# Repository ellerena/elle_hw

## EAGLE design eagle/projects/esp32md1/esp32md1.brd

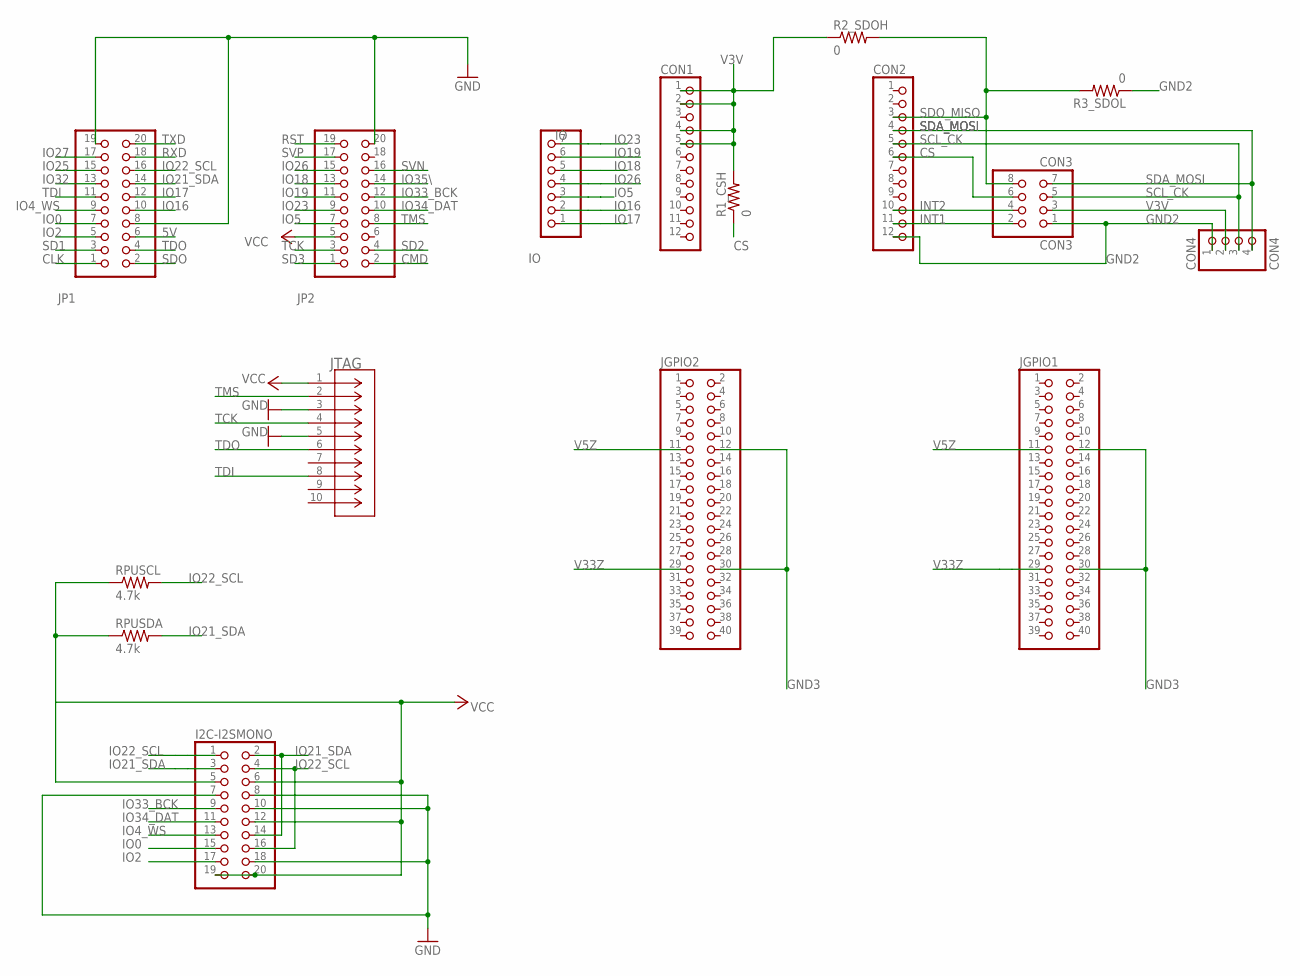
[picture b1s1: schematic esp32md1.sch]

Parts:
CON1, CON2: PINHD-1X12; 1X12
CON3: CON3; 2X04
CON4: CON4; 1X04
I2C-I2SMONO: PINHD-2X10; 2X10
IO: IO; 1X07
JGPIO1, JGPIO2: PINHD-2X20; 2X20
JP1, JP2: PINHD-2X10; 2X10
JTAG: M50-3600542CONN_M50-3600542_HRW-L; CONN_M50-3600542_HRW-L
R1_CSH, R2_SDOH, R3_SDOL: 0; R0402
RPUSCL: 4.7k; R0402
RPUSDA: 4.7k; R0402

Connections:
5V: JP1.6
CLK: JP1.1
CMD: JP2.2
CS: CON2.6, CON3.6, R1_CSH.1
GND: I2C-I2SMONO.7, I2C-I2SMONO.8, I2C-I2SMONO.10, I2C-I2SMONO.18, JP1.8, JP1.19, JP2.20, JTAG.3, JTAG.5
GND2: CON2.12, CON3.1, CON4.1, R3_SDOL.1
GND3: JGPIO1.12, JGPIO1.30, JGPIO2.12, JGPIO2.30
INT1: CON2.11, CON3.2
INT2: CON2.10, CON3.4
IO0: I2C-I2SMONO.15, JP1.7
IO2: I2C-I2SMONO.17, JP1.5
IO4_WS: I2C-I2SMONO.13, JP1.9
IO5: IO.3, JP2.7
IO16: IO.2, JP1.10
IO17: IO.1, JP1.12
IO18: IO.5, JP2.13
IO19: IO.6, JP2.11
IO21_SDA: I2C-I2SMONO.2, I2C-I2SMONO.3, I2C-I2SMONO.14, JP1.14, RPUSDA.2
IO22_SCL: I2C-I2SMONO.1, I2C-I2SMONO.4, I2C-I2SMONO.16, JP1.16, RPUSCL.2
IO23: IO.7, JP2.9
IO25: JP1.15
IO26: IO.4, JP2.15
IO27: JP1.17
IO32: JP1.13
IO33_BCK: I2C-I2SMONO.9, JP2.12
IO34_DAT: I2C-I2SMONO.11, JP2.10
IO35\: JP2.14
RST: JP2.19
RXD: JP1.18
SCL_CK: CON2.5, CON3.5, CON4.3
SD1: JP1.3
SD2: JP2.4
SD3: JP2.1
SDA_MOSI: CON2.4, CON3.7, CON4.4
SDO: JP1.2
SDO_MISO: CON2.3, CON3.8, R2_SDOH.2, R3_SDOL.2
SVN: JP2.16
SVP: JP2.17
TCK: JP2.3, JTAG.4
TDI: JP1.11, JTAG.8
TDO: JP1.4, JTAG.6
TMS: JP2.8, JTAG.2
TXD: JP1.20
V3V: CON1.1, CON1.2, CON1.4, CON1.5, CON3.3, CON4.2, R1_CSH.2, R2_SDOH.1
V5Z: JGPIO1.11, JGPIO2.11
V33Z: JGPIO1.29, JGPIO2.29
VCC: I2C-I2SMONO.5, I2C-I2SMONO.6, I2C-I2SMONO.12, I2C-I2SMONO.19, I2C-I2SMONO.20, JP2.5, JTAG.1, RPUSCL.1, RPUSDA.1

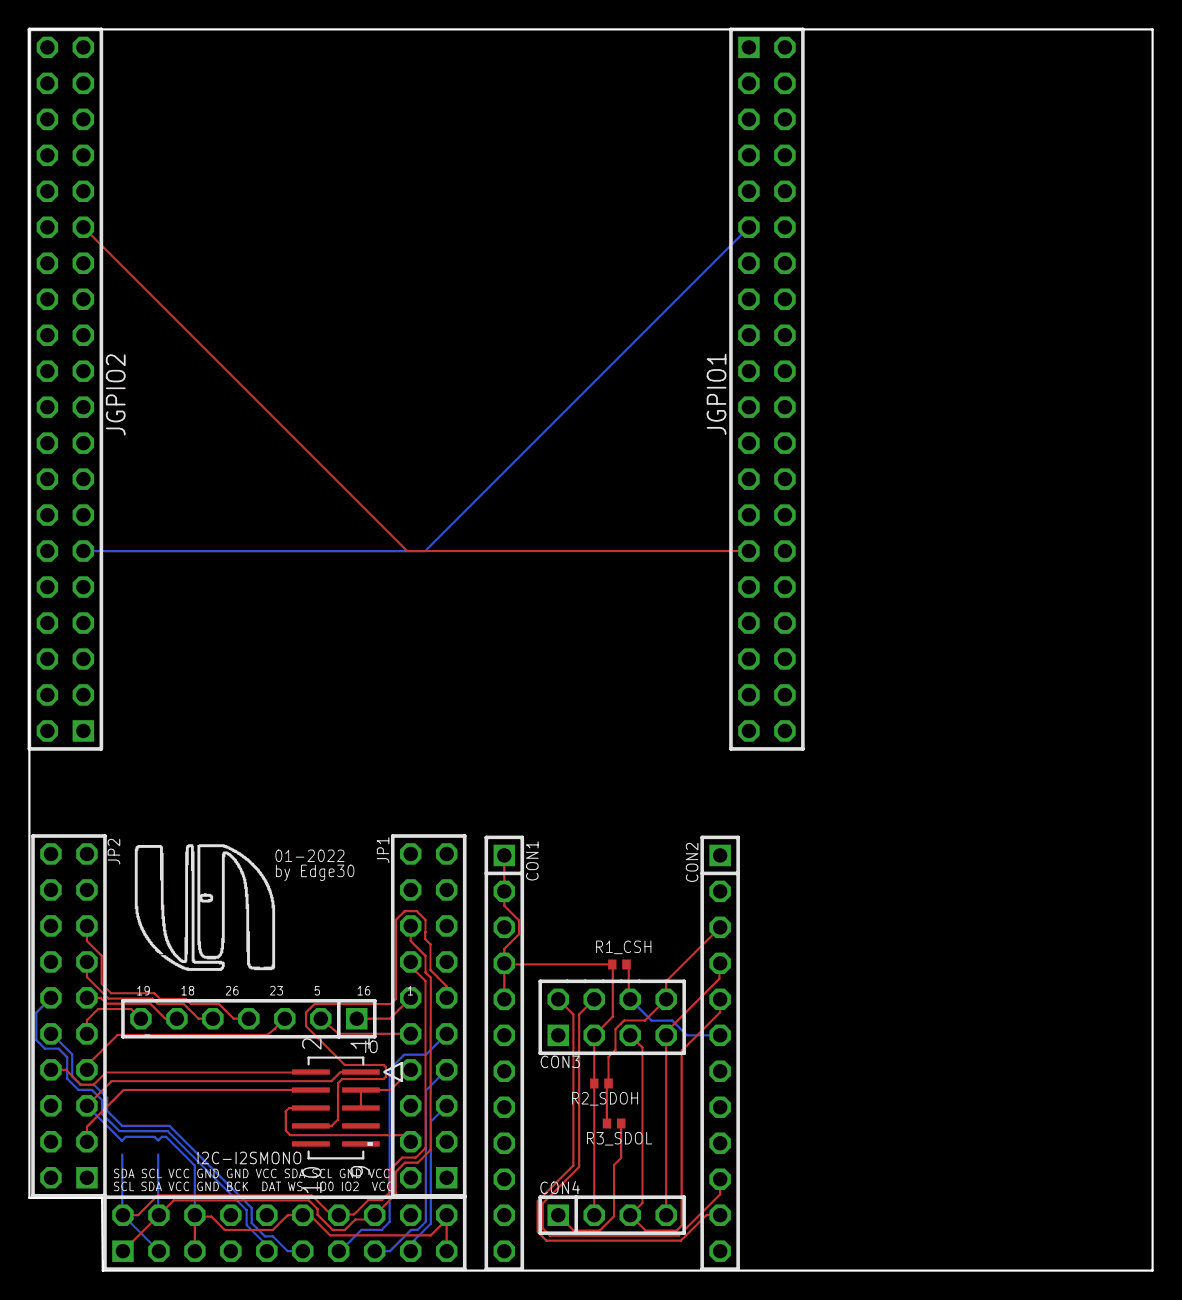
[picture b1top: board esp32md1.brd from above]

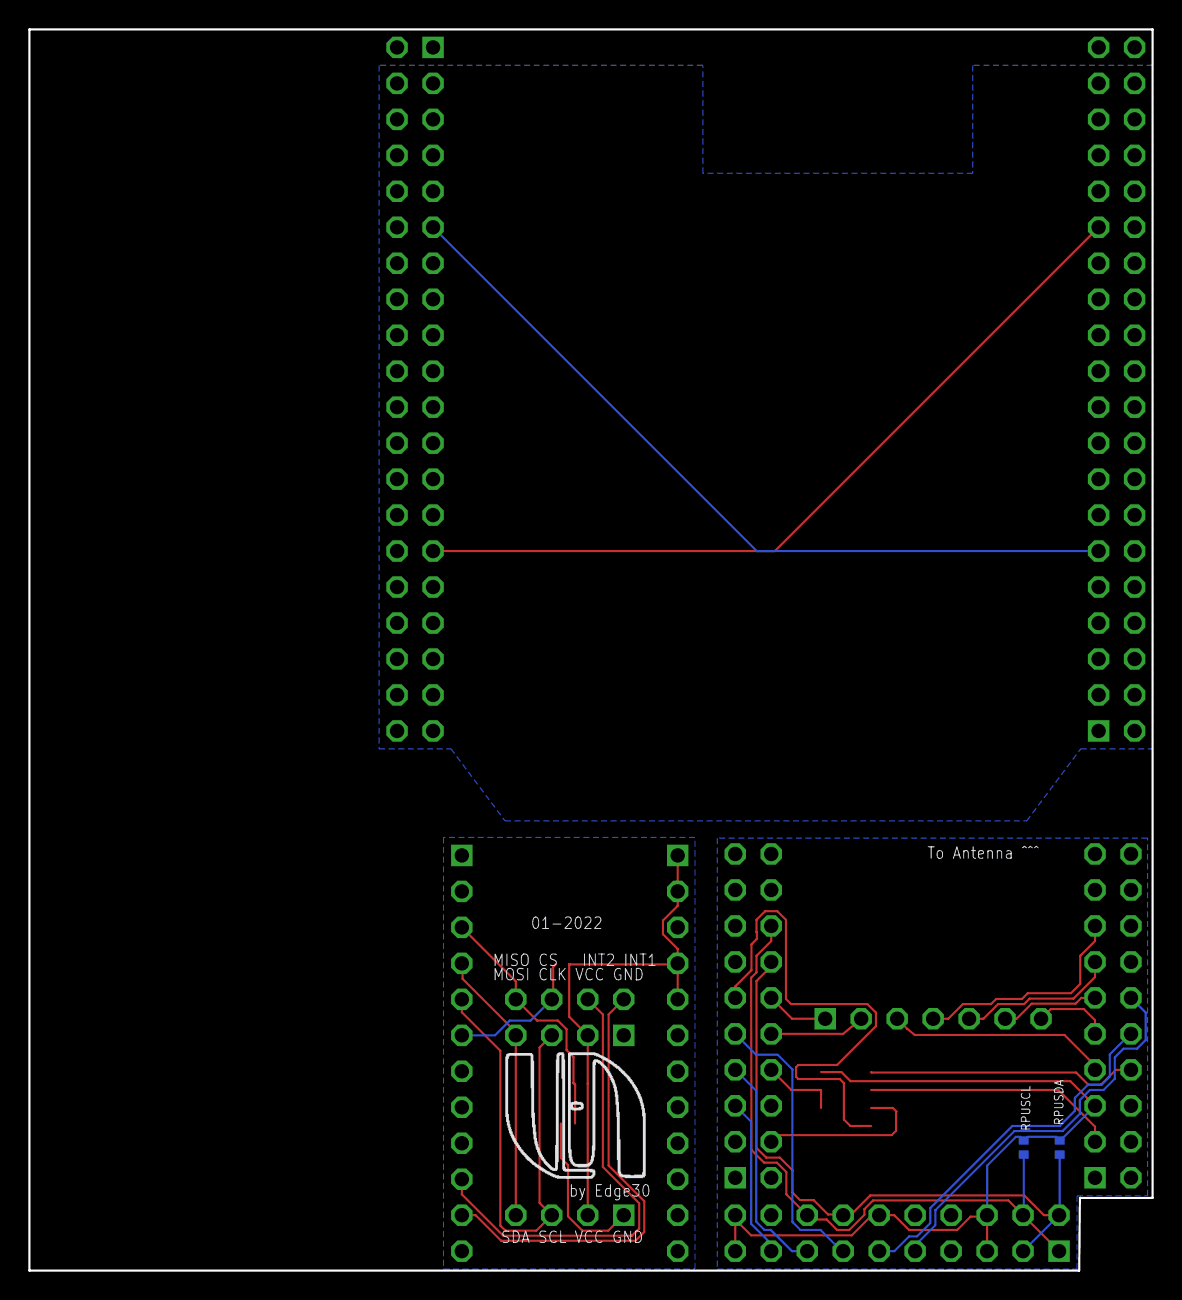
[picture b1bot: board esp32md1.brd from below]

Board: 2 copper layers, 79.3 x 87.6 mm, 16 parts (2 on the bottom side), 31 nets.

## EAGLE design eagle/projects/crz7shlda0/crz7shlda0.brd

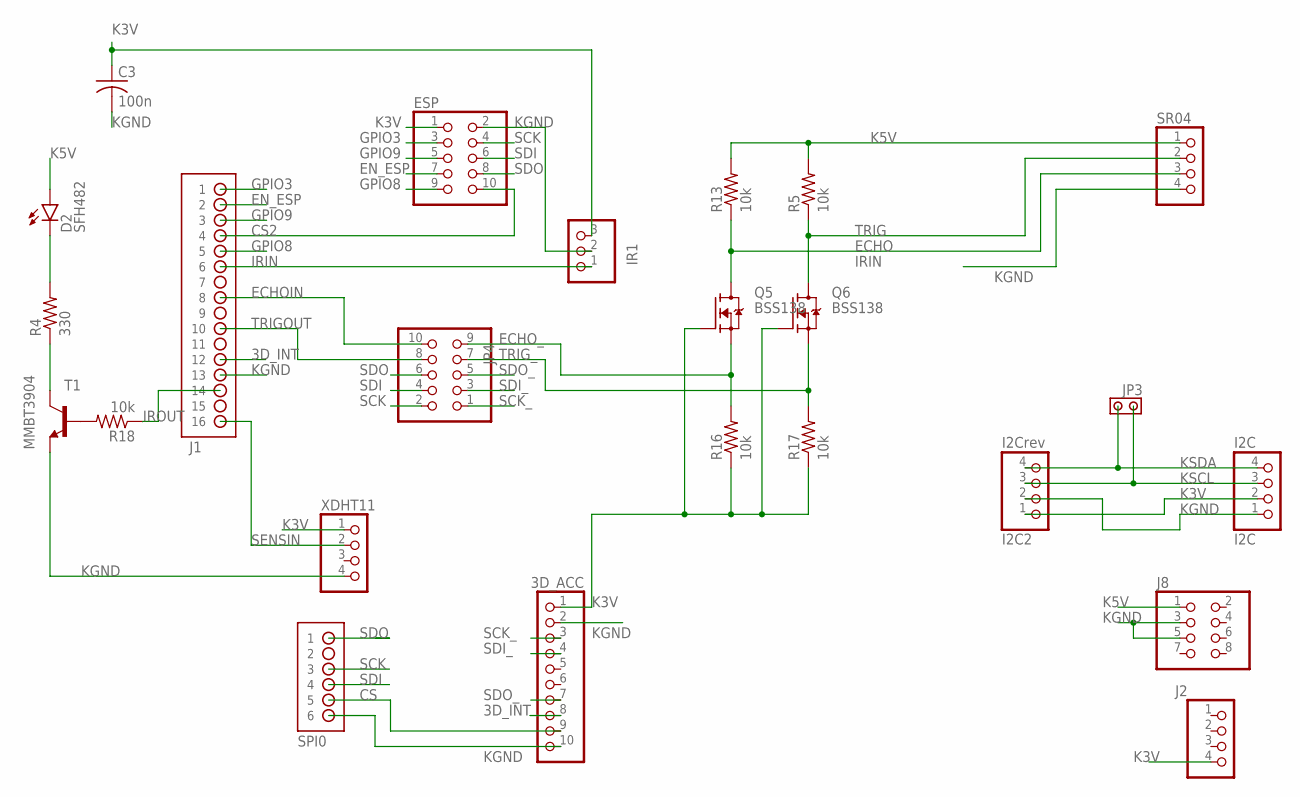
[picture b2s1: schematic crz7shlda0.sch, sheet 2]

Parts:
3D_ACC: PINHD-1X10; 1X10
C3: 100n; C0402
D2: SFH482
ESP: PINHD-2X5; 2X05
I2C: I2C; 1X04
I2C2: I2Crev; 1X04
IR1: PINHD-1X3; 1X03
J1: HDR-2X8
J2: PINHD-1X4; 1X04
J8: PINHD-2X4; 2X04
JP3: JPR-1X2
JP4: PINHD-2X5; 2X05
Q5, Q6: BSS138; SOT23
R4: 330; R0402
R5, R13, R16, R17, R18: 10k; R0402
SPI0: HDR-2X3
SR04: PINHD-1X4; 1X04
T1: MMBT3904; SOT23-BEC
XDHT11: PINHD-1X4; 1X04

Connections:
3D_INT: 3D_ACC.8, J1.12
CS: 3D_ACC.9, SPI0.5
CS2: ESP.10, J1.4
ECHO: Q5.3 (D), R13.1, SR04.3
ECHOIN: J1.8, JP4.10
ECHO_: JP4.9, Q5.2 (S), R16.2
EN_ESP: ESP.7, J1.2
GPIO3: ESP.3, J1.1
GPIO8: ESP.9, J1.5
GPIO9: ESP.5, J1.3
IRIN: IR1.1, J1.6
IROUT: J1.14, R18.1
K3V: 3D_ACC.1, C3.1, ESP.1, I2C.2, I2C2.1, IR1.3, J2.4, Q5.1 (G), Q6.1 (G), R16.1, R17.1, XDHT11.1
K5V: D2.A, J8.1, R5.2, R13.2, SR04.1
KGND: 3D_ACC.2, 3D_ACC.10, C3.2, ESP.2, I2C.1, I2C2.2, IR1.2, J1.13, J8.3, J8.5, SPI0.6, SR04.4, T1.E, XDHT11.4
KSCL: I2C.3, I2C2.3, JP3.2
KSDA: I2C.4, I2C2.4, JP3.1
unnamed: R4.1, T1.C
unnamed: D2.K (C), R4.2
unnamed: R18.2, T1.B
SCK: ESP.4, JP4.2, SPI0.3
SCK_: 3D_ACC.3, JP4.1
SDI: ESP.6, JP4.4, SPI0.4
SDI_: 3D_ACC.4, JP4.3
SDO: ESP.8, JP4.6, SPI0.1
SDO_: 3D_ACC.7, JP4.5
SENSIN: J1.16, XDHT11.2
TRIG: Q6.3 (D), R5.1, SR04.2
TRIGOUT: J1.10, JP4.8
TRIG_: JP4.7, Q6.2 (S), R17.2

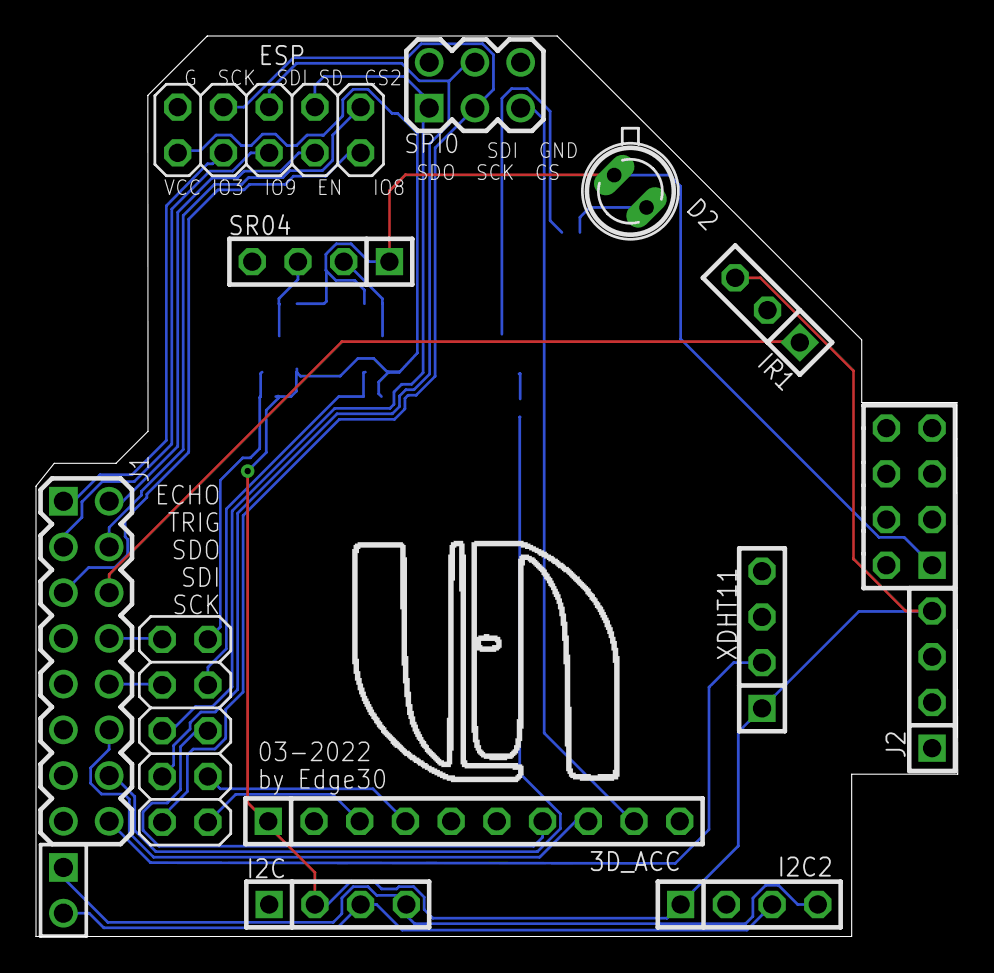
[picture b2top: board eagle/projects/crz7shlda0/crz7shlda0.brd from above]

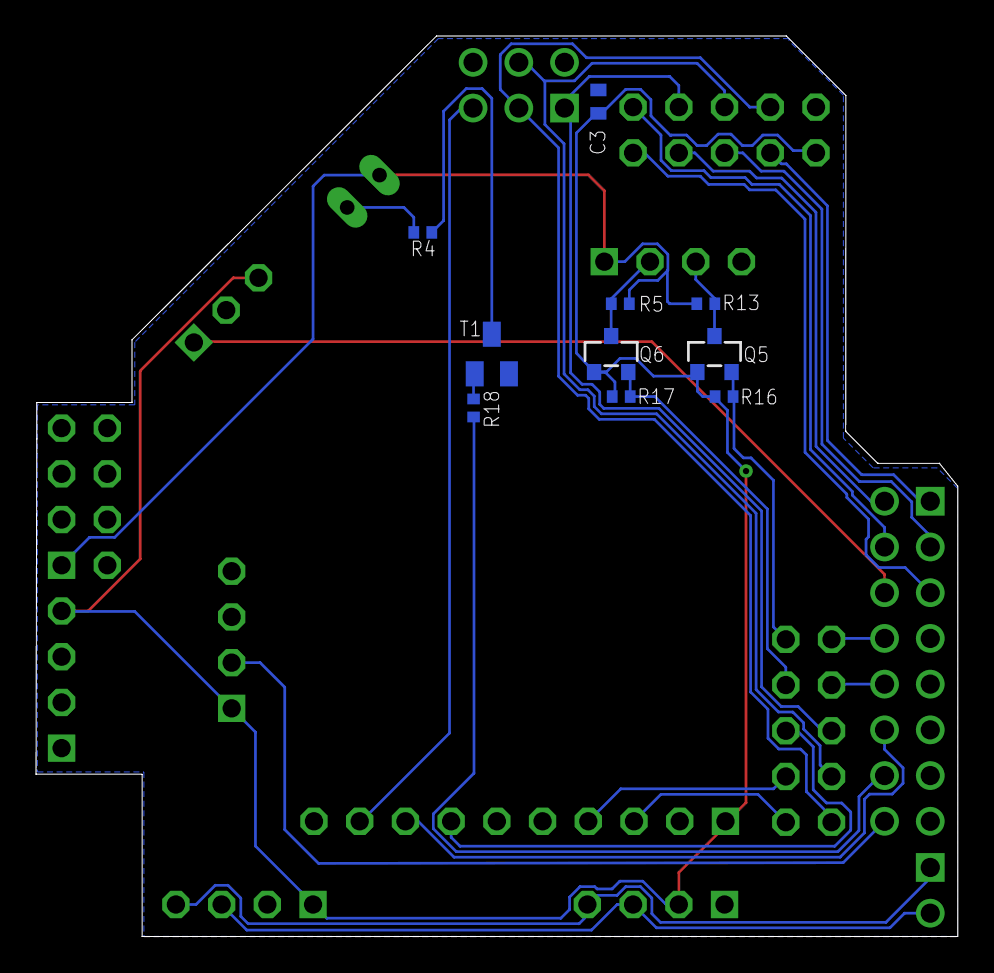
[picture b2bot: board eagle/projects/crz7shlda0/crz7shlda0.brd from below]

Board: 2 copper layers, 51.2 x 50.0 mm, 24 parts (10 on the bottom side), 30 nets.

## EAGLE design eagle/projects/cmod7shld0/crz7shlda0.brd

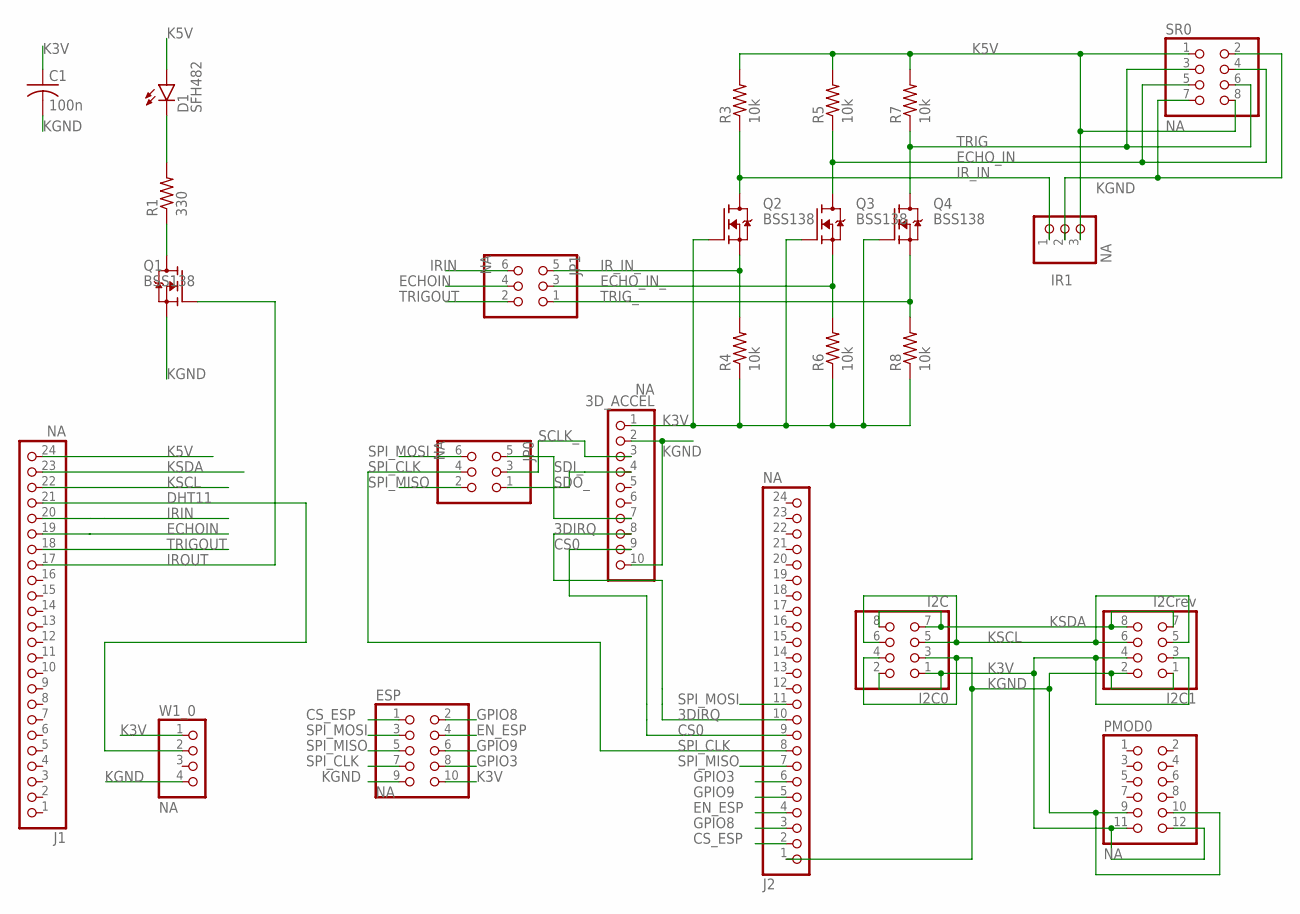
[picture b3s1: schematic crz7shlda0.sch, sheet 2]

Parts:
3D_ACCEL: NA; 1X10
C1: 100n; C0402
D1: SFH482
ESP: NA; 2X05
I2C0: I2C; 2X04
I2C1: I2Crev; 2X04
IR1: NA; 1X03
J1, J2: NA; 1X24
JP0, JP1: NA; 2X03
PMOD0: NA; 2X06
Q1, Q2, Q3, Q4: BSS138; SOT23
R1: 330; R0402
R3, R4, R5, R6, R7, R8: 10k; R0402
SR0: NA; 2X04
W1_0: NA; 1X04

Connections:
3DIRQ: 3D_ACCEL.8, J2.10
CS0: 3D_ACCEL.9, J2.9
CS_ESP: ESP.1, J2.2
DHT11: J1.21, W1_0.2
ECHOIN: J1.19, JP1.4
ECHO_IN: Q3.3 (D), R5.1, SR0.4, SR0.5
ECHO_IN_: JP1.3, Q3.2 (S), R6.2
EN_ESP: ESP.4, J2.4
GPIO3: ESP.8, J2.6
GPIO8: ESP.2, J2.3
GPIO9: ESP.6, J2.5
IRIN: J1.20, JP1.6
IROUT: J1.17, Q1.1 (G)
IR_IN: IR1.1, Q2.3 (D), R3.1
IR_IN_: JP1.5, Q2.2 (S), R4.2
K3V: 3D_ACCEL.1, C1.1, ESP.10, I2C0.1, I2C0.2, I2C1.3, I2C1.4, PMOD0.11, PMOD0.12, Q2.1 (G), Q3.1 (G), Q4.1 (G), R4.1, R6.1, R8.1, W1_0.1
K5V: D1.A, IR1.3, J1.24, R3.2, R5.2, R7.2, SR0.1, SR0.8
KGND: 3D_ACCEL.2, 3D_ACCEL.10, C1.2, ESP.9, I2C0.3, I2C0.4, I2C1.1, I2C1.2, IR1.2, J2.1, PMOD0.9, PMOD0.10, Q1.2 (S), SR0.2, SR0.7, W1_0.4
KSCL: I2C0.5, I2C0.6, I2C1.5, I2C1.6, J1.22
KSDA: I2C0.7, I2C0.8, I2C1.7, I2C1.8, J1.23
unnamed: Q1.3 (D), R1.1
unnamed: D1.K (C), R1.2
SCLK_: 3D_ACCEL.3, JP0.3
SDI_: 3D_ACCEL.4, JP0.1
SDO_: 3D_ACCEL.7, JP0.5
SPI_CLK: ESP.7, J2.8, JP0.4
SPI_MISO: ESP.5, J2.7, JP0.2
SPI_MOSI: ESP.3, J2.11, JP0.6
TRIG: Q4.3 (D), R7.1, SR0.3, SR0.6
TRIGOUT: J1.18, JP1.2
TRIG_: JP1.1, Q4.2 (S), R8.2

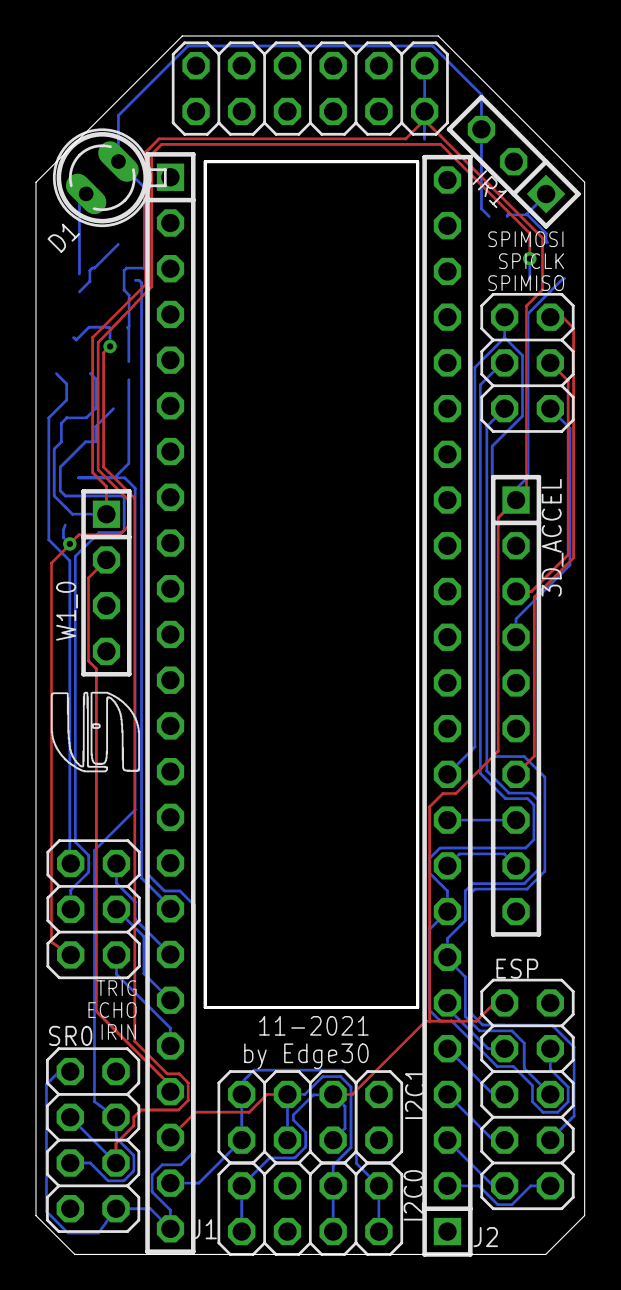
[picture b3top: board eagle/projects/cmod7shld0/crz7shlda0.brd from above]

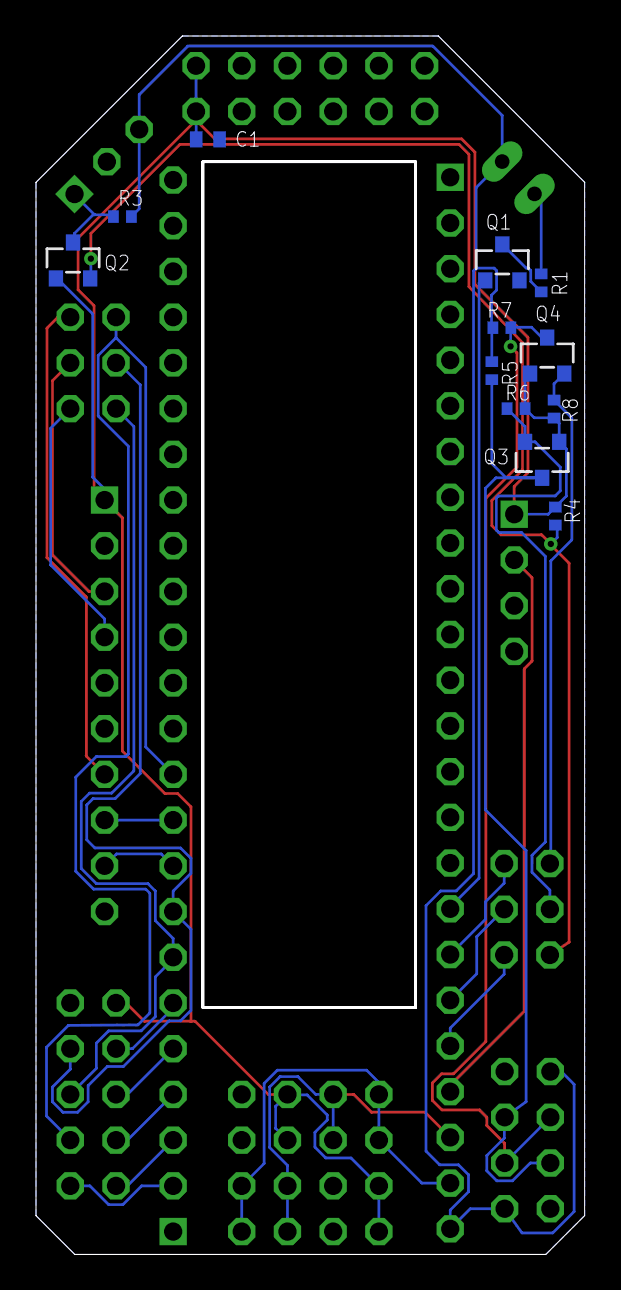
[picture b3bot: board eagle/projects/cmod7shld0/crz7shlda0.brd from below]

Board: 2 copper layers, 30.3 x 67.5 mm, 25 parts (12 on the bottom side), 31 nets.

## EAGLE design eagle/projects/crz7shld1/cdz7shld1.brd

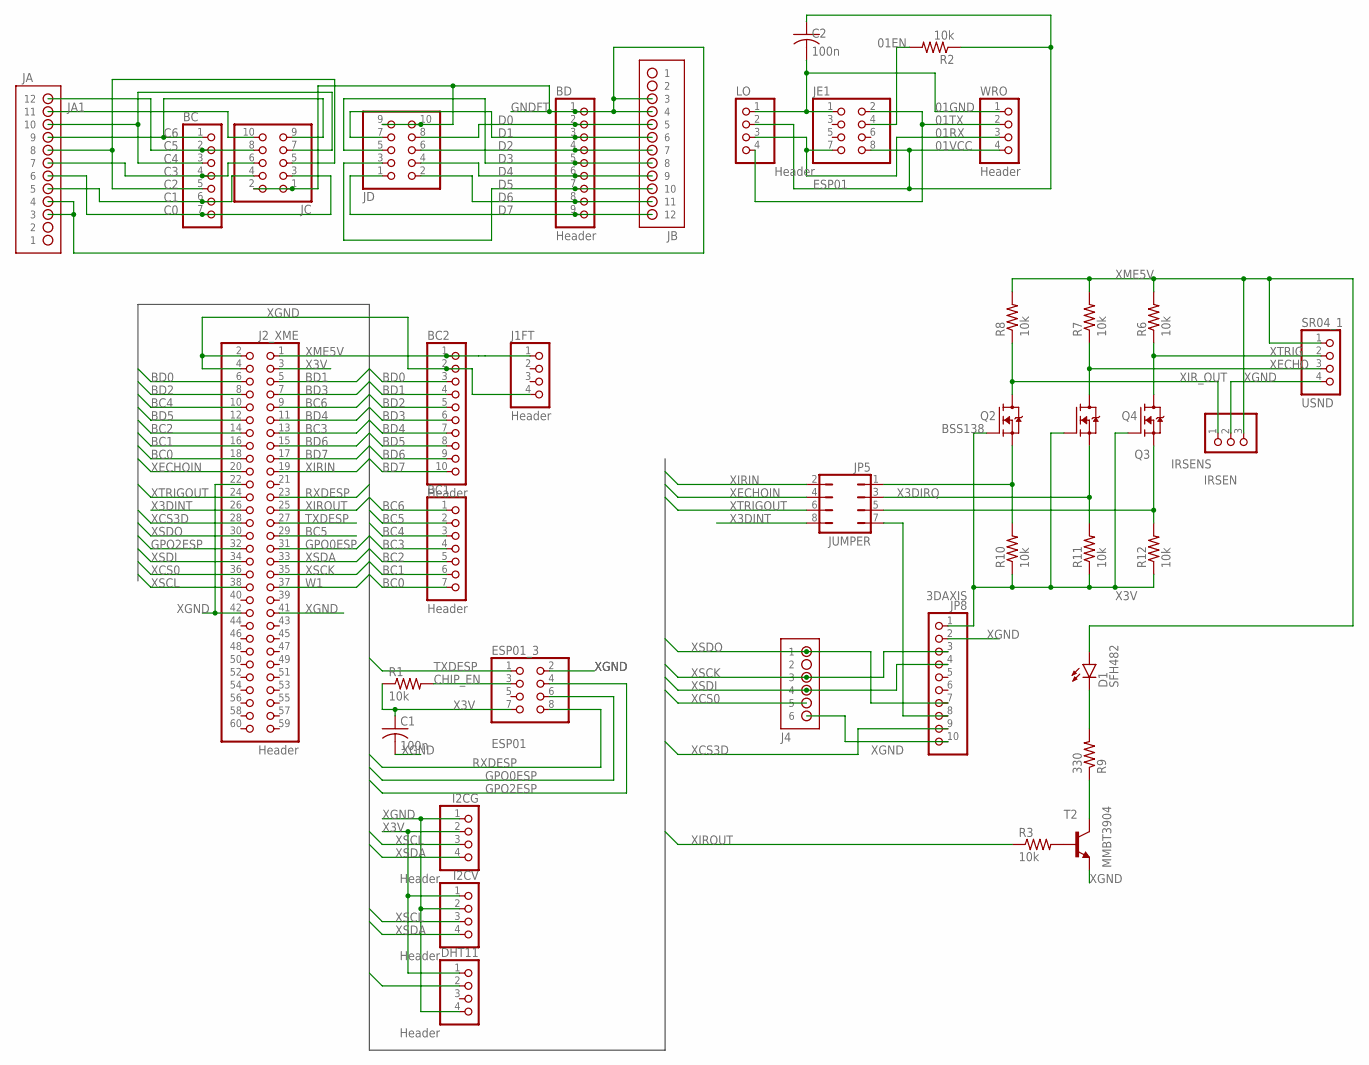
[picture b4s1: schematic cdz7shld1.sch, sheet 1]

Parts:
BC, BC1: Header; 1X07
BC2: Header; 1X10
BD: Header; 1X09
C1, C2: 100n; C0402
D1: SFH482
DHT11: Header; 1X04
ESP01_3: ESP01; 2X04
I2CG, I2CV: Header; 1X04
IRSENS: IRSEN; 1X03
J1FT: Header; 1X04
J2_XME: Header; 2X30
J4: HDR-2X3
JA: HDR-2X6
JB: HDR-2X6
JC: Header; 2X05
JD: Header; 2X05
JE1: ESP01; 2X04
JP5: JUMPER; JP4Q
JP8: 3DAXIS; 1X10
LO: Header; 1X04
Q2, Q3, Q4: BSS138; SOT23
R1, R2, R3, R6, R7, R8, R10, R11, R12: 10k; R0402
R9: 330; R0402
SR04_1: USND; 1X04
T2: MMBT3904; SOT23-BEC
WRO: Header; 1X04

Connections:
01EN: JE1.4, R2.2
01GND: C2.2, JE1.1, LO.1, WRO.1
01RX: JE1.7, LO.3, WRO.3
01TX: JE1.2, LO.4, WRO.2
01VCC: C2.1, JE1.8, LO.2, R2.1, WRO.4
BC0: BC1.7, J2_XME.18
BC1: BC1.6, J2_XME.16
BC2: BC1.5, J2_XME.14
BC3: BC1.4, J2_XME.13
BC4: BC1.3, J2_XME.10
BC5: BC1.2, J2_XME.29
BC6: BC1.1, J2_XME.9
BD0: BC2.3, J2_XME.6
BD1: BC2.4, J2_XME.5
BD2: BC2.5, J2_XME.8
BD3: BC2.6, J2_XME.7
BD4: BC2.7, J2_XME.11
BD5: BC2.8, J2_XME.12
BD6: BC2.9, J2_XME.15
BD7: BC2.10, J2_XME.17
C0: BC.7, JA.6, JC.3
C1: BC.6, JA.5, JC.4
C2: BC.5, JA.8, JC.5
C3: BC.4, JA.7, JC.6
C4: BC.3, JA.10, JC.7
C5: BC.2, JA.12, JC.8
C6: BC.1, JA.9, JC.9
CHIP_EN: ESP01_3.3, R1.2
D0: BD.2, JB.5, JD.8
D1: BD.3, JB.6, JD.7
D2: BD.4, JB.7, JD.6
D3: BD.5, JB.8, JD.5
D4: BD.6, JB.9, JD.4
D5: BD.7, JB.10, JD.3
D6: BD.8, JB.11, JD.2
D7: BD.9, JB.12, JD.1
GNDFT: BD.1, JA.3, JA.4, JB.3, JB.4, JC.1, JC.2, JD.9, JD.10
GPO0ESP: ESP01_3.6, J2_XME.31
GPO2ESP: ESP01_3.4, J2_XME.32
JA1: JA.11, JC.10
unnamed: D1.K (C), R9.2
unnamed: JP5.1, Q2.2 (S), R10.2
unnamed: R3.2, T2.B
unnamed: JP5.3, Q3.2 (S), R11.2
unnamed: JP5.5, Q4.2 (S), R12.2
unnamed: R9.1, T2.C
RXDESP: ESP01_3.8, J2_XME.23
TXDESP: ESP01_3.1, J2_XME.27
W1: DHT11.2, J2_XME.37
X3DINT: J2_XME.26, JP5.8
X3DIRQ: JP5.7, JP8.8
X3V: C1.1, DHT11.1, ESP01_3.7, I2CG.2, I2CV.1, J2_XME.3, JP8.1, Q2.1 (G), Q3.1 (G), Q4.1 (G), R1.1, R10.1, R11.1, R12.1
XCS0: J2_XME.36, J4.5
XCS3D: J2_XME.28, JP8.9
XECHO: Q3.3 (D), R7.1, SR04_1.3
XECHOIN: J2_XME.20, JP5.4
XGND: BC2.2, C1.2, DHT11.4, ESP01_3.2, I2CG.1, I2CV.2, IRSENS.2, J1FT.4, J2_XME.2, J2_XME.4, J2_XME.22, J2_XME.41, J2_XME.42, J4.6, JP8.2, JP8.10, SR04_1.4, T2.E
XIRIN: J2_XME.19, JP5.2
XIROUT: J2_XME.25, R3.1
XIR_OUT: IRSENS.1, Q2.3 (D), R8.1
XME5V: BC2.1, D1.A, IRSENS.3, J1FT.1, J2_XME.1, R6.2, R7.2, R8.2, SR04_1.1
XSCK: J2_XME.35, J4.3, JP8.3
XSCL: I2CG.3, I2CV.3, J2_XME.38
XSDA: I2CG.4, I2CV.4, J2_XME.33
XSDI: J2_XME.34, J4.4, JP8.4
XSDO: J2_XME.30, J4.1, JP8.7
XTRIG: Q4.3 (D), R6.1, SR04_1.2
XTRIGOUT: J2_XME.24, JP5.6

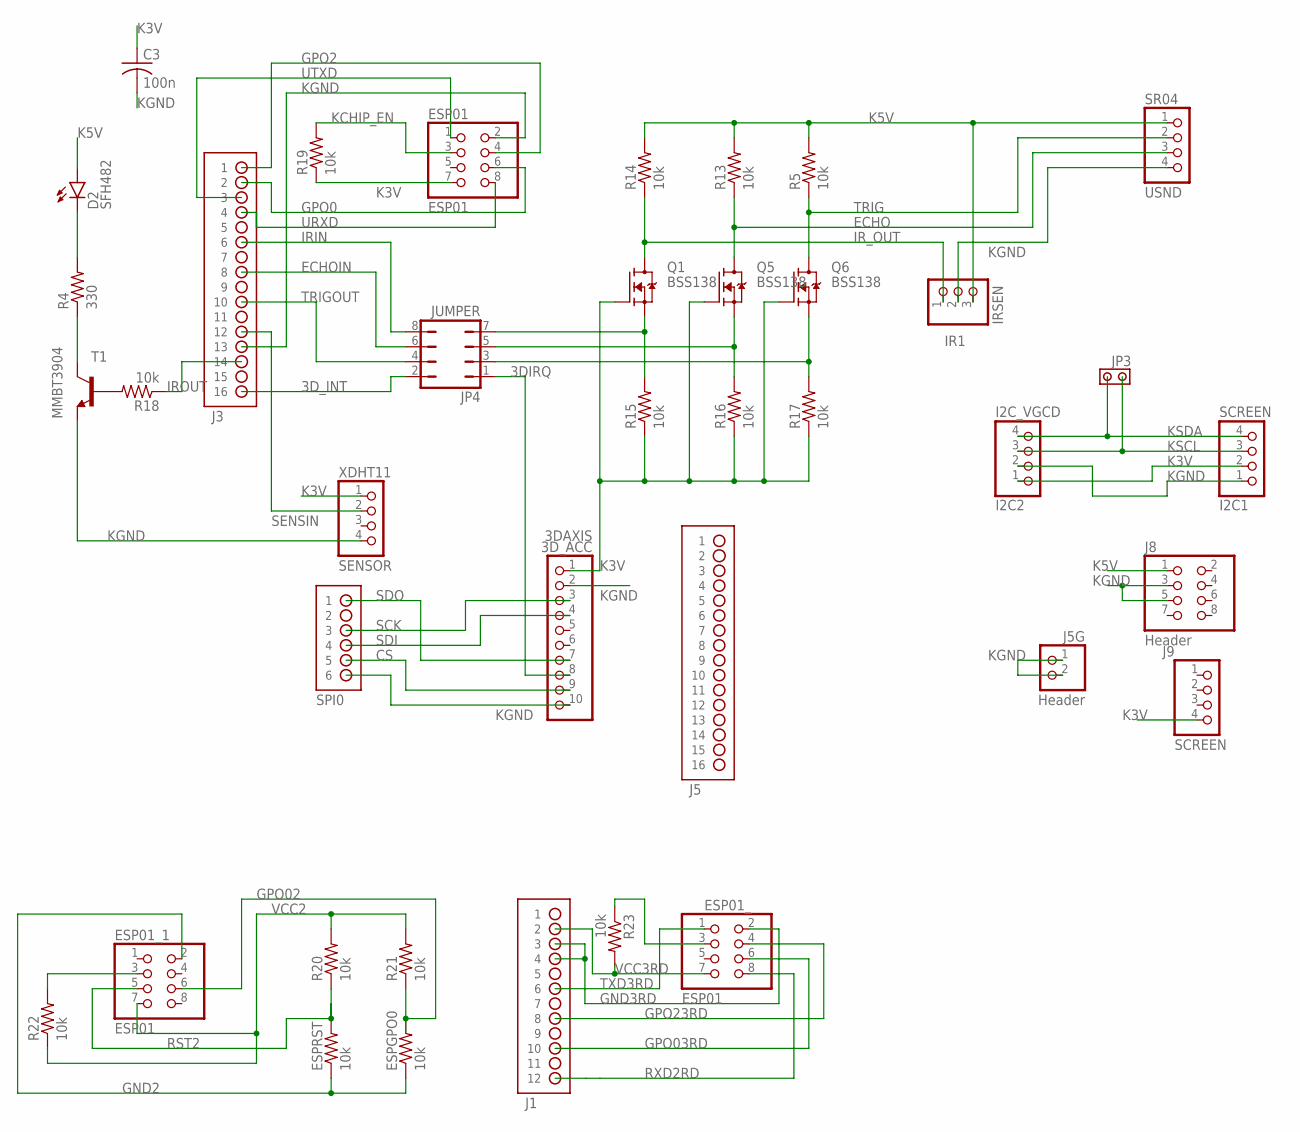
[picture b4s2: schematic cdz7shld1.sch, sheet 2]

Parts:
3D_ACC: 3DAXIS; 1X10
C3: 100n; C0402
D2: SFH482
ESP01, ESP01_, ESP01_1: ESP01; 2X04
ESPGPO0: 10k; 0204/5
ESPRST: 10k; 0204/5
I2C1: SCREEN; 1X04
I2C2: I2C_VGCD; 1X04
IR1: IRSEN; 1X03
J1: HDR-2X6
J3, J5: HDR-2X8
J5G: Header; 1X02
J8: Header; 2X04
J9: SCREEN; 1X04
JP3: JPR-1X2
JP4: JUMPER; JP4Q
Q1, Q5, Q6: BSS138; SOT23
R4: 330; R0402
R5, R13, R14, R15, R16, R17, R18, R19, R20, R21, R22, R23: 10k; R0402
SPI0: HDR-2X3
SR04: USND; 1X04
T1: MMBT3904; SOT23-BEC
XDHT11: SENSOR; 1X04

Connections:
3DIRQ: 3D_ACC.8, JP4.1
3D_INT: J3.16, JP4.2
CS: 3D_ACC.9, SPI0.5
ECHO: Q5.3 (D), R13.1, SR04.3
ECHOIN: J3.8, JP4.6
GND2: ESP01_1.2, ESPGPO0.1, ESPRST.1
GND3RD: ESP01_.2, J1.3, J1.4
GPO0: ESP01.6, J3.2
GPO2: ESP01.4, J3.1
GPO02: ESP01_1.6, ESPGPO0.2, R21.1
GPO03RD: ESP01_.6, J1.10
GPO23RD: ESP01_.4, J1.8
IRIN: J3.6, JP4.8
IROUT: J3.14, R18.1
IR_OUT: IR1.1, Q1.3 (D), R14.1
K3V: 3D_ACC.1, C3.1, ESP01.7, I2C1.2, I2C2.1, J9.4, Q1.1 (G), Q5.1 (G), Q6.1 (G), R15.1, R16.1, R17.1, R19.1, XDHT11.1
K5V: D2.A, IR1.3, J8.1, R5.2, R13.2, R14.2, SR04.1
KCHIP_EN: ESP01.3, R19.2
KGND: 3D_ACC.2, 3D_ACC.10, C3.2, ESP01.2, I2C1.1, I2C2.2, IR1.2, J3.13, J5G.1, J5G.2, J8.3, J8.5, SPI0.6, SR04.4, T1.E, XDHT11.4
KSCL: I2C1.3, I2C2.3, JP3.2
KSDA: I2C1.4, I2C2.4, JP3.1
unnamed: R4.1, T1.C
unnamed: D2.K (C), R4.2
unnamed: JP4.5, Q5.2 (S), R16.2
unnamed: JP4.3, Q6.2 (S), R17.2
unnamed: JP4.7, Q1.2 (S), R15.2
unnamed: R18.2, T1.B
unnamed: ESP01_1.3, R22.2
unnamed: ESP01_.3, R23.1
RST2: ESP01_1.5, ESPRST.2, R20.1
RXD2RD: ESP01_.8, J1.12
SCK: 3D_ACC.3, SPI0.3
SDI: 3D_ACC.4, SPI0.4
SDO: 3D_ACC.7, SPI0.1
SENSIN: J3.12, XDHT11.2
TRIG: Q6.3 (D), R5.1, SR04.2
TRIGOUT: J3.10, JP4.4
TXD3RD: ESP01_.1, J1.6
URXD: ESP01.8, J3.4
UTXD: ESP01.1, J3.3
VCC2: ESP01_1.7, R20.2, R21.2, R22.1
VCC3RD: ESP01_.7, J1.2, R23.2

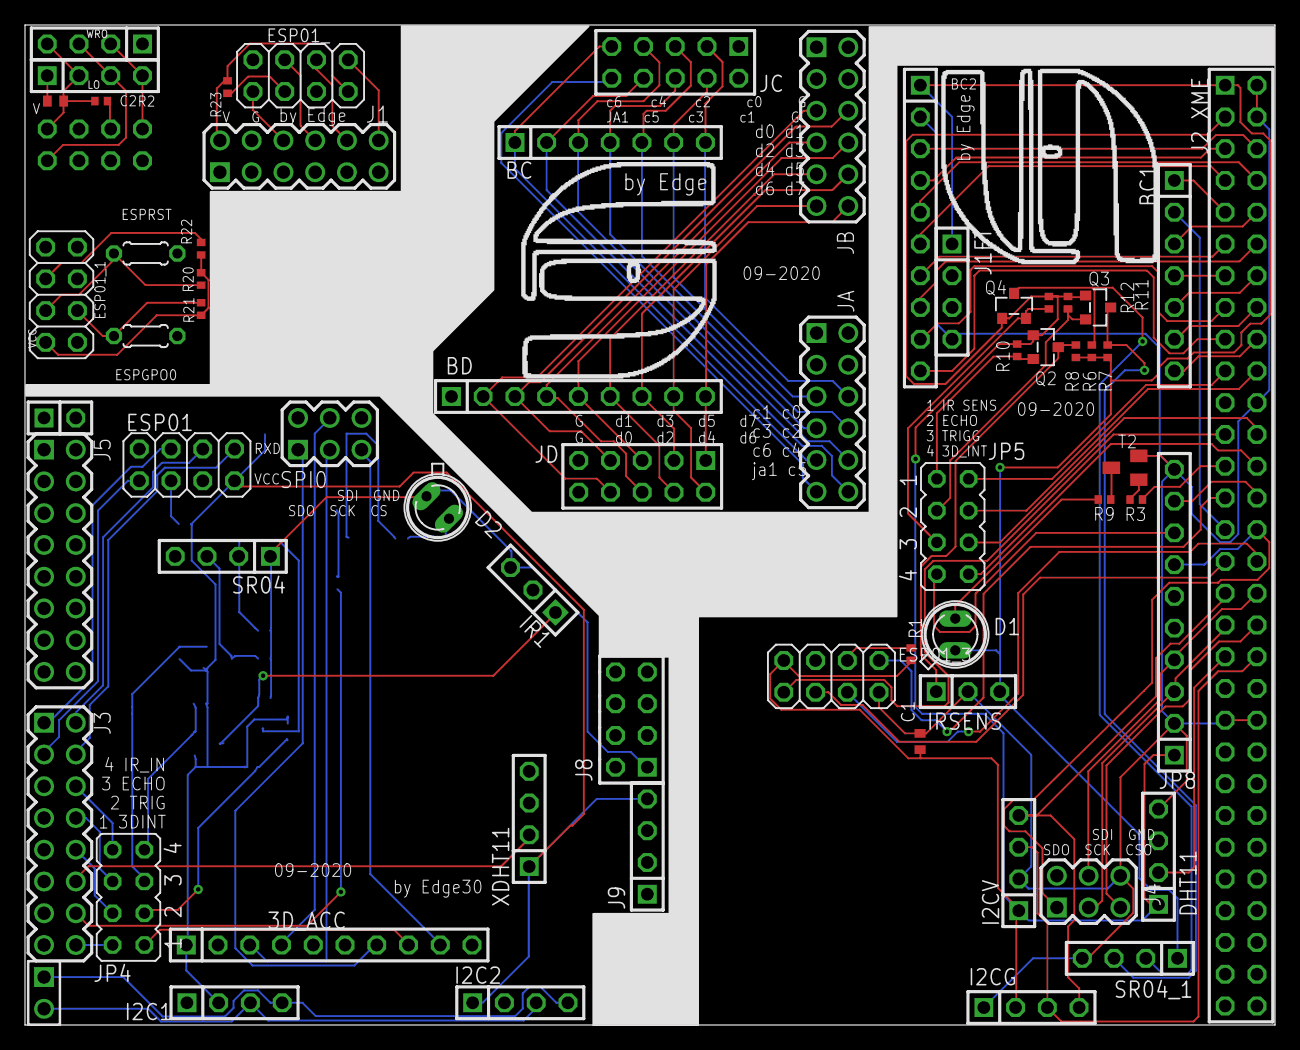
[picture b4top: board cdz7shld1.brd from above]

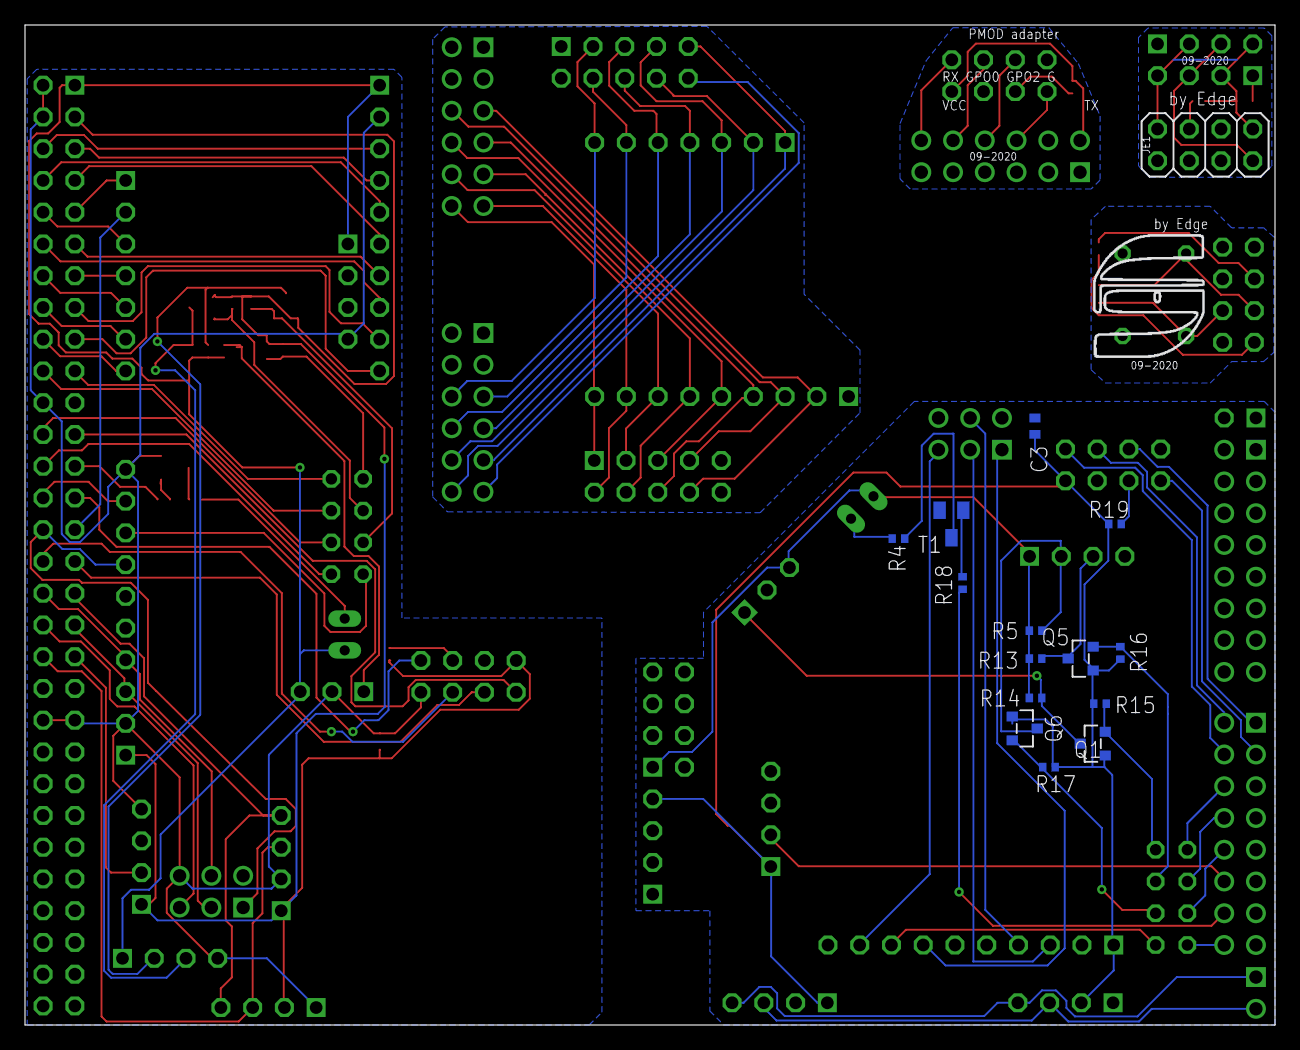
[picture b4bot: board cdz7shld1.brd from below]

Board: 2 copper layers, 100.0 x 80.0 mm, 78 parts (15 on the bottom side), 110 nets.

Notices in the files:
parts and their libraries:
diy-modules_new: Released under the Creative Commons Attribution 4.0 International License: http://creativecommons.org/licenses/by/4.0
COPYRIGHT: Copyright (C) 2023 Ultra Librarian. All rights reserved.
